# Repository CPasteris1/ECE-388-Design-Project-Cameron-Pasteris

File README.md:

# ECE-388-Design-Project-Cameron-Pasteris
Github Repository for ECE 388 Design Project

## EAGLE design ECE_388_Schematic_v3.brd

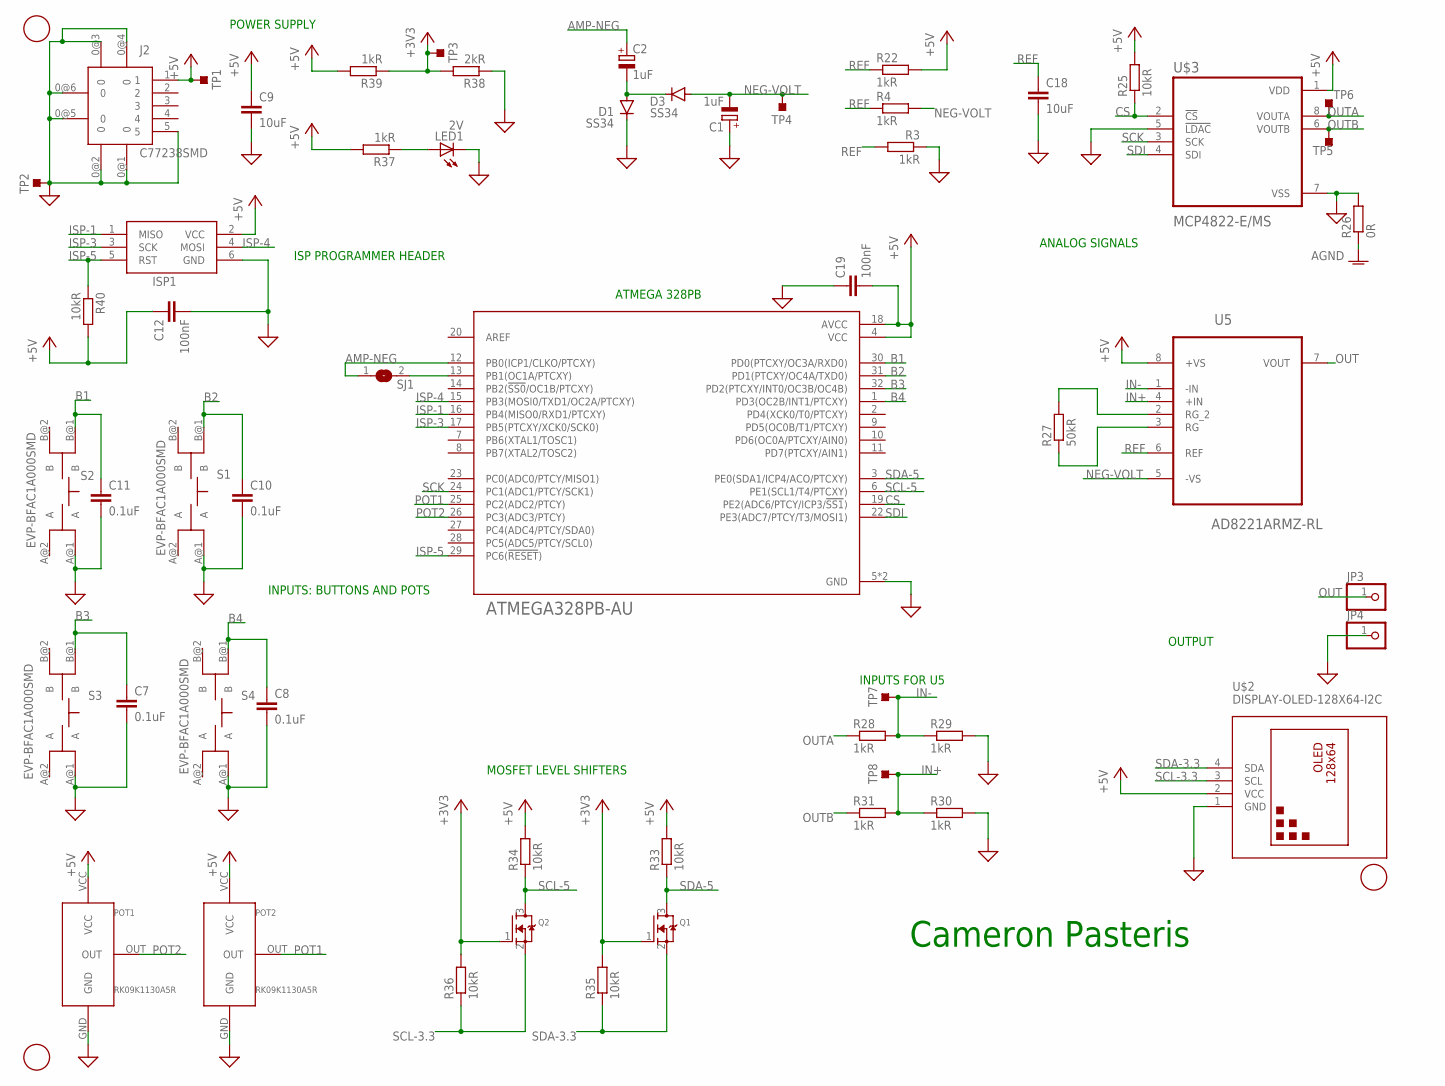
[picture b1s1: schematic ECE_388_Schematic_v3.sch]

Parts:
C1, C2: 1uF; E2,5-6E
C7, C8, C10, C11: 0.1uF; C0805
C9, C18: 10uF; C0805
C12, C19: 100nF; C0805
D1, D3: SS34; DO-214AC
F1, F2, F3: FIDUCIAL; FIDUCIAL_1MM
ISP1: AVRISP-6; AVRISP
J2: C77238SMD; C77238
JP3, JP4: PINHD-1X1; 1X01
LED1: 2V; CHIP-LED0805
POT1, POT2: RK09K1130A5R
Q1, Q2: MOSFET-NREFLOW; SOT23
R3, R4, R22, R28, R29, R30, R31, R37, R39: 1kR; R0805
R25, R33, R34, R35, R36, R40: 10kR; R0805
R26: 0R; R0805
R27: 50kR; R0805
R38: 2kR; R0805
S1, S2, S3, S4: EVP-BFAC1A000SMD; EVP-BFAC1A000
SJ1: SJ
TP1, TP2, TP3, TP4, TP5, TP6, TP7, TP8: TESTPOINT_TPS-PAD-036; TESTPOINT_PAD-036
U1: ATMEGA328PB-AU; QFP80P900X900X120-32N
U5: AD8221ARMZ-RL; SOP65P490X110-8N
U$2: DISPLAY-OLED-128X64-I2C
U$3: MCP4822-E/MS; SOP65P490X110-8N

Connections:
+3V3: Q1.1 (G), Q2.1 (G), R35.2, R36.2, R38.2, R39.1, TP3.1
+5V: C9.1, C12.1, C19.2, ISP1.2 (VCC), J2.1, POT1.VCC, POT2.VCC, R22.2, R25.2, R33.2, R34.2, R37.2, R39.2, R40.2, TP1.1, U1.4 (VCC), U1.18 (AVCC), U5.8 (+VS), U$2.2 (VCC), U$3.1 (VDD)
AGND: R26.1
AMP-NEG: C2.+, SJ1.1, U1.12 (PB0(ICP1/CLKO/PTCXY))
B1: C11.1, S2.B@1 (B), U1.30 (PD0(PTCXY/OC3A/RXD0))
B2: C10.1, S1.B@1 (B), U1.31 (PD1(PTCXY/OC4A/TXD0))
B3: C7.1, S3.B@1 (B), U1.32 (PD2(PTCXY/INT0/OC3B/OC4B))
B4: C8.1, S4.B@1 (B), U1.1 (PD3(OC2B/INT1/PTCXY))
CS: R25.1, U1.19 (PE2(ADC6/PTCY/ICP3/!SS1!)), U$3.2 (!CS)
GND: C1.+, C7.2, C8.2, C9.2, C10.2, C11.2, C12.2, C18.2, C19.1, D1.C, ISP1.6 (GND), J2.0@1 (0), J2.0@2 (0), J2.0@3 (0), J2.0@4 (0), J2.0@5 (0), J2.0@6 (0), J2.5, JP4.1, LED1.C, POT1.GND, POT2.GND, R3.1, R26.2, R29.2, R30.2, R38.1, S1.A@1 (A), S2.A@1 (A), S3.A@1 (A), S4.A@1 (A), TP2.1, U1.5 (GND), U1.21 (GND), U$2.1 (GND), U$3.5 (!LDAC), U$3.7 (VSS)
IN+: R30.1, R31.2, TP8.1, U5.4 (+IN)
IN-: R28.2, R29.1, TP7.1, U5.1 (-IN)
ISP-1: ISP1.1 (MISO), U1.16 (PB4(MISO0/RXD1/PTCXY))
ISP-3: ISP1.3 (SCK), U1.17 (PB5(PTCXY/XCK0/SCK0))
ISP-4: ISP1.4 (MOSI), U1.15 (PB3(MOSI0/TXD1/OC2A/PTCXY))
ISP-5: ISP1.5 (RST), R40.1, U1.29 (PC6(!RESET!))
unnamed: R27.2, U5.2 (RG_2)
unnamed: LED1.A, R37.1
unnamed: R27.1, U5.3 (RG)
unnamed: C2.-, D1.A, D3.C
unnamed: SJ1.2, U1.13 (PB1(OC1A/PTCXY))
NEG-VOLT: C1.-, D3.A, R4.2, TP4.1, U5.5 (-VS)
OUT: JP3.1, U5.7 (VOUT)
OUTA: R28.1, TP6.1, U$3.8 (VOUTA)
OUTB: R31.1, TP5.1, U$3.6 (VOUTB)
POT1: POT2.OUT, U1.25 (PC2(ADC2/PTCY))
POT2: POT1.OUT, U1.26 (PC3(ADC3/PTCY))
REF: C18.1, R3.2, R4.1, R22.1, U5.6 (REF)
SCK: U1.24 (PC1(ADC1/PTCY/SCK1)), U$3.3 (SCK)
SCL-3.3: Q2.2 (S), R36.1, U$2.3 (SCL)
SCL-5: Q2.3 (D), R34.1, U1.6 (PE1(SCL1/T4/PTCXY))
SDA-3.3: Q1.2 (S), R35.1, U$2.4 (SDA)
SDA-5: Q1.3 (D), R33.1, U1.3 (PE0(SDA1/ICP4/ACO/PTCXY))
SDI: U1.22 (PE3(ADC7/PTCY/T3/MOSI1)), U$3.4 (SDI)

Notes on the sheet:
Cameron Pasteris
POWER SUPPLY
ISP PROGRAMMER HEADER
INPUTS: BUTTONS AND POTS
MOSFET LEVEL SHIFTERS
ANALOG SIGNALS
OUTPUT
INPUTS FOR U5
ATMEGA 328PB

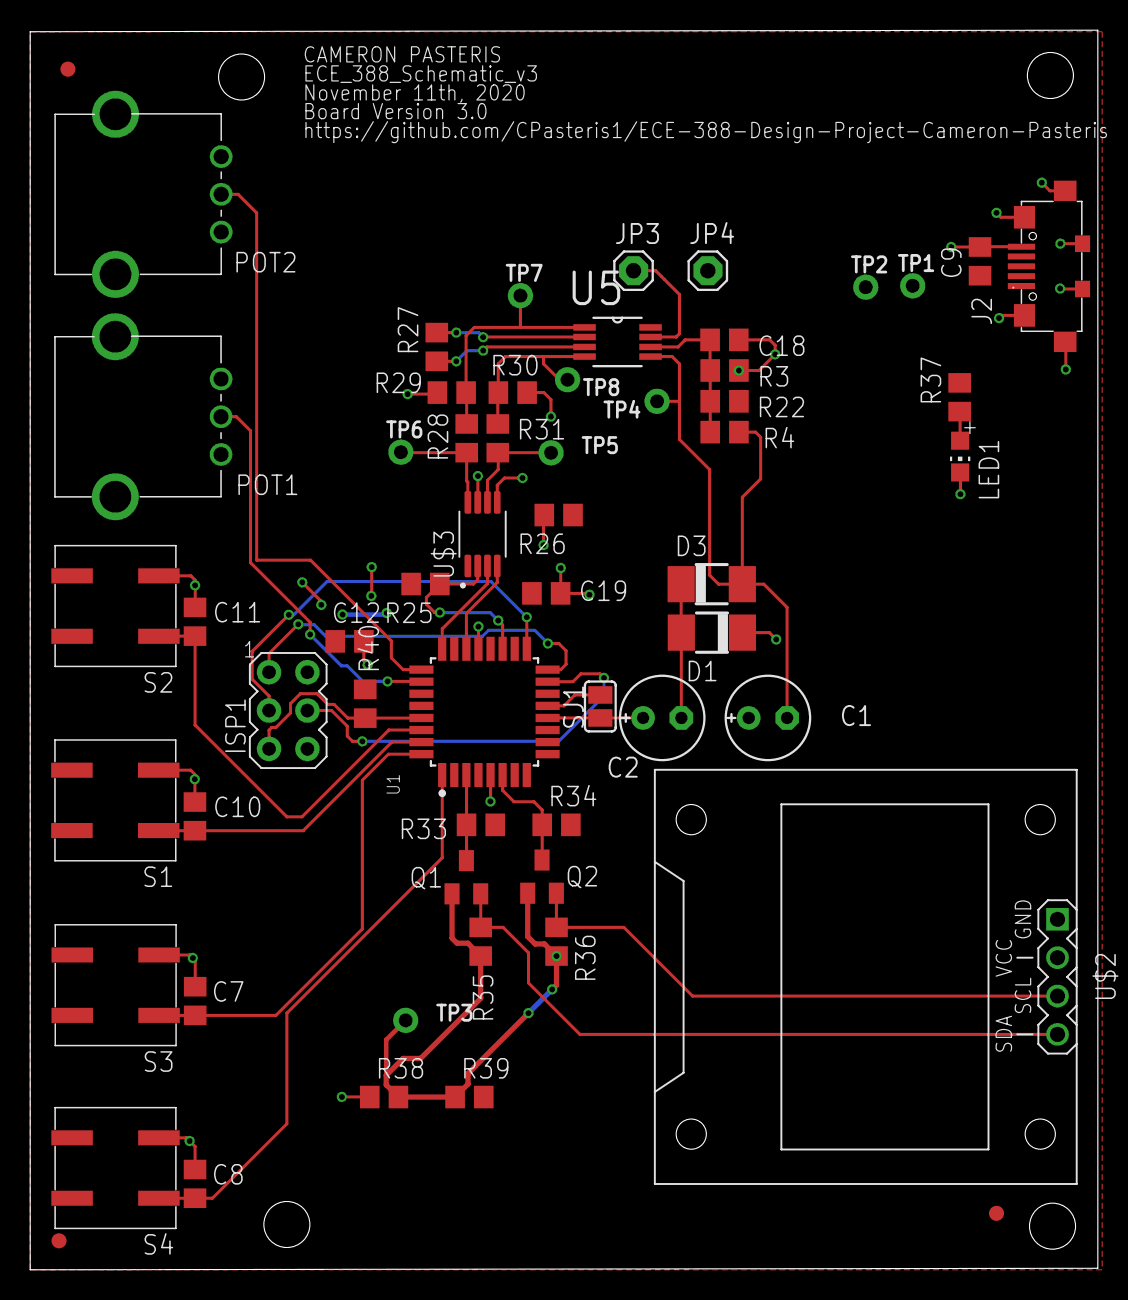
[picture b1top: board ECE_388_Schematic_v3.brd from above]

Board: 2 copper layers, 70.7 x 82.1 mm, 59 parts (0 on the bottom side), 33 nets.

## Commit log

2020-12-08 Create DemoVideoLink

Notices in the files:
parts and their libraries:
diy-modules: Released under the Creative Commons Attribution 4.0 International License: http://creativecommons.org/licenses/by/4.0
